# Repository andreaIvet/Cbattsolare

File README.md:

# Cbattsolare
battCharge:Simple electric bike 42 VDC battery on off control for  48 VDC (12x4) solar panels 
motorDriverigbtGrande:Igbt Motor board solar panel + capacitor + attiny85 pmw controller

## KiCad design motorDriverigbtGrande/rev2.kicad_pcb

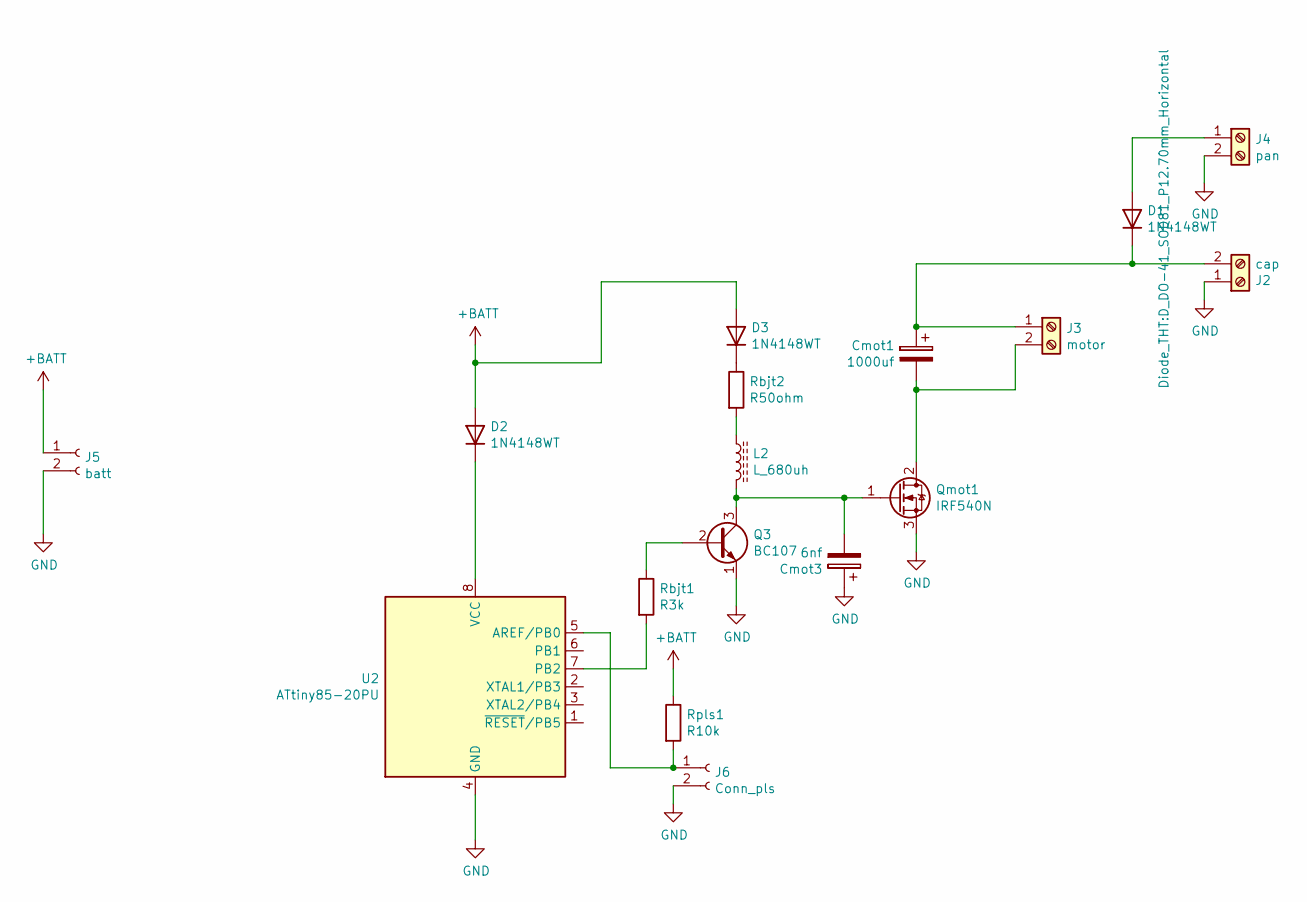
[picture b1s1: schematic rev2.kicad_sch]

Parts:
Cmot1: 1000uf; CP_Radial_D12.5mm_P5.00mm
Cmot3: 6nf; C_Disc_D3.0mm_W2.0mm_P2.50mm
D1: 1N4148WT; D_DO-41_SOD81_P12.70mm_Horizontal
D2, D3: 1N4148WT; D_DO-34_SOD68_P7.62mm_Horizontal
J2: cap; TerminalBlock_Phoenix_MKDS-1,5-2_1x02_P5.00mm_Horizontal
J3: motor; TerminalBlock_Phoenix_MKDS-1,5-2_1x02_P5.00mm_Horizontal
J4: pan; TerminalBlock_Phoenix_MKDS-1,5-2_1x02_P5.00mm_Horizontal
J5: batt; PinHeader_1x02_P2.54mm_Vertical
J6: Conn_pls; PinHeader_1x02_P2.54mm_Vertical
L2: L_680uh; L_Axial_L6.6mm_D2.7mm_P2.54mm_Vertical_Vishay_IM-2
Q3: BC107; TO-92_Inline_Wide
Qmot1: IRF540N; TO-247-3_Vertical
Rbjt1: R3k; R_Axial_DIN0204_L3.6mm_D1.6mm_P7.62mm_Horizontal
Rbjt2: R50ohm; R_Axial_DIN0204_L3.6mm_D1.6mm_P7.62mm_Horizontal
Rpls1: R10k; R_Axial_DIN0204_L3.6mm_D1.6mm_P7.62mm_Horizontal
U2: ATtiny85-20PU; DIP-8_W7.62mm

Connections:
+BATT: D2.2 (A), D3.2 (A), J5.1, Rpls1.1
GND: Cmot3.1, J2.1, J4.2, J5.2, J6.2, Q3.1 (E), Qmot1.3 (S), U2.4 (GND)
unnamed: Cmot1.1, D1.1 (K), J2.2, J3.1
unnamed: Cmot1.2, J3.2, Qmot1.2 (D)
unnamed: Cmot3.2, L2.2, Q3.3 (C), Qmot1.1 (G)
unnamed: D1.2 (A), J4.1
unnamed: D3.1 (K), Rbjt2.1
unnamed: J6.1, Rpls1.2, U2.5 (AREF/PB0)
unnamed: L2.1, Rbjt2.2
unnamed: Q3.2 (B), Rbjt1.1
unnamed: Rbjt1.2, U2.7 (PB2)
unnamed: D2.1 (K), U2.8 (VCC)

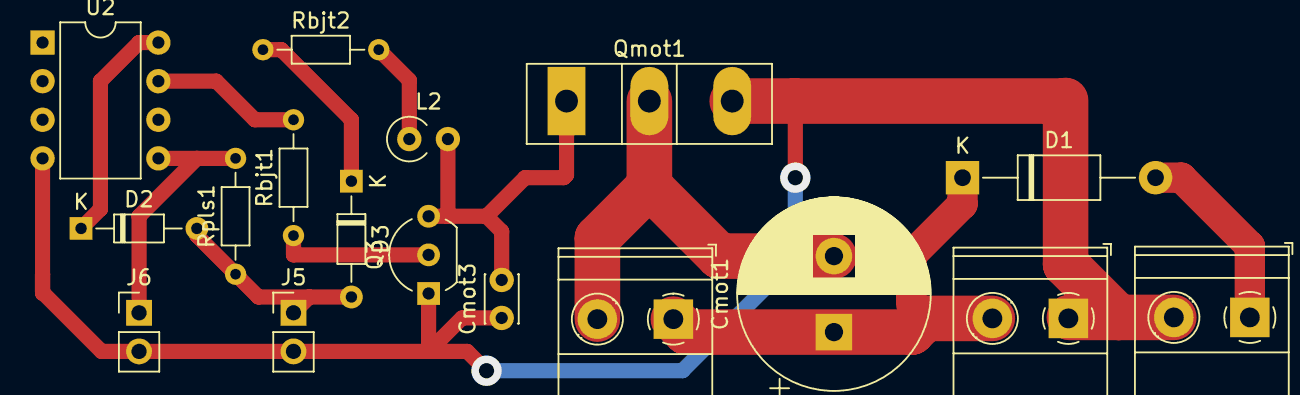
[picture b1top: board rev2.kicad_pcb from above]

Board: 2 copper layers, 17 parts (0 on the bottom side), 12 nets.

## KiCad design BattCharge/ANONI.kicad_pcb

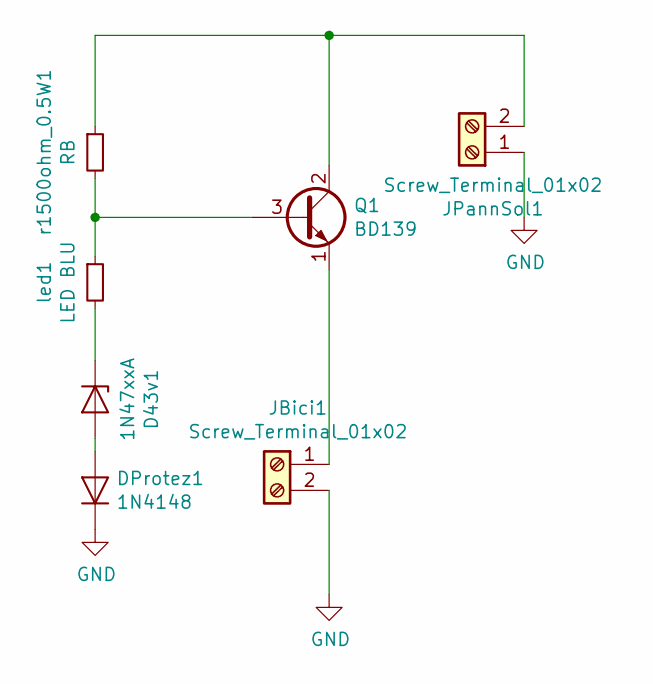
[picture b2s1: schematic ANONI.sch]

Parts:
D43v1: 1N47xxA; D_T-1_P5.08mm_Horizontal
DProtez1: 1N4148; D_DO-35_SOD27_P7.62mm_Horizontal
JBici1: Screw_Terminal_01x02; TerminalBlock_Phoenix_PT-1,5-2-5.0-H_1x02_P5.00mm_Horizontal
JPannSol1: Screw_Terminal_01x02; TerminalBlock_Phoenix_PT-1,5-2-5.0-H_1x02_P5.00mm_Horizontal
Q1: BD139; TO-126-3_Vertical
led1: LED BLU; D_DO-35_SOD27_P2.54mm_Vertical_AnodeUp
r1500ohm_0.5W1: RB; R_Axial_DIN0414_L11.9mm_D4.5mm_P15.24mm_Horizontal

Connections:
GND: DProtez1.1 (K), JBici1.2, JPannSol1.1
unnamed: D43v1.1 (K), led1.2
unnamed: D43v1.2 (A), DProtez1.2 (A)
unnamed: JBici1.1, Q1.1 (E)
unnamed: JPannSol1.2, Q1.2 (C), r1500ohm_0.5W1.1
unnamed: Q1.3 (B), led1.1, r1500ohm_0.5W1.2

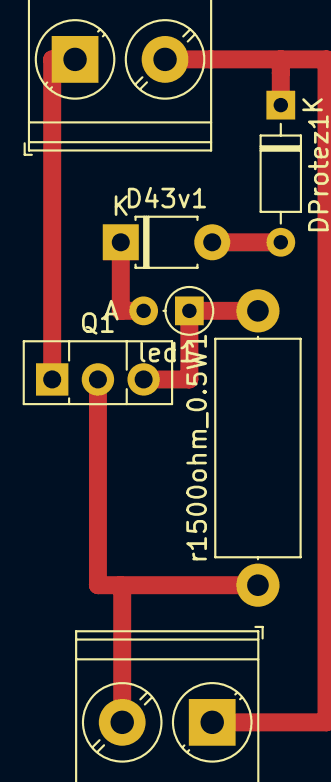
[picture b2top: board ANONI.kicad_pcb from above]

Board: 2 copper layers, 7 parts (0 on the bottom side), 6 nets.

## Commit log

2024-05-05 version 0
2026-05-06 motorDriver
